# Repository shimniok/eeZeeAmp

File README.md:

eeZeeAmp is a breakout board for a standard LM386 audio amplifier circuit making it convenient to add audio
amplification to your breadboard projects.

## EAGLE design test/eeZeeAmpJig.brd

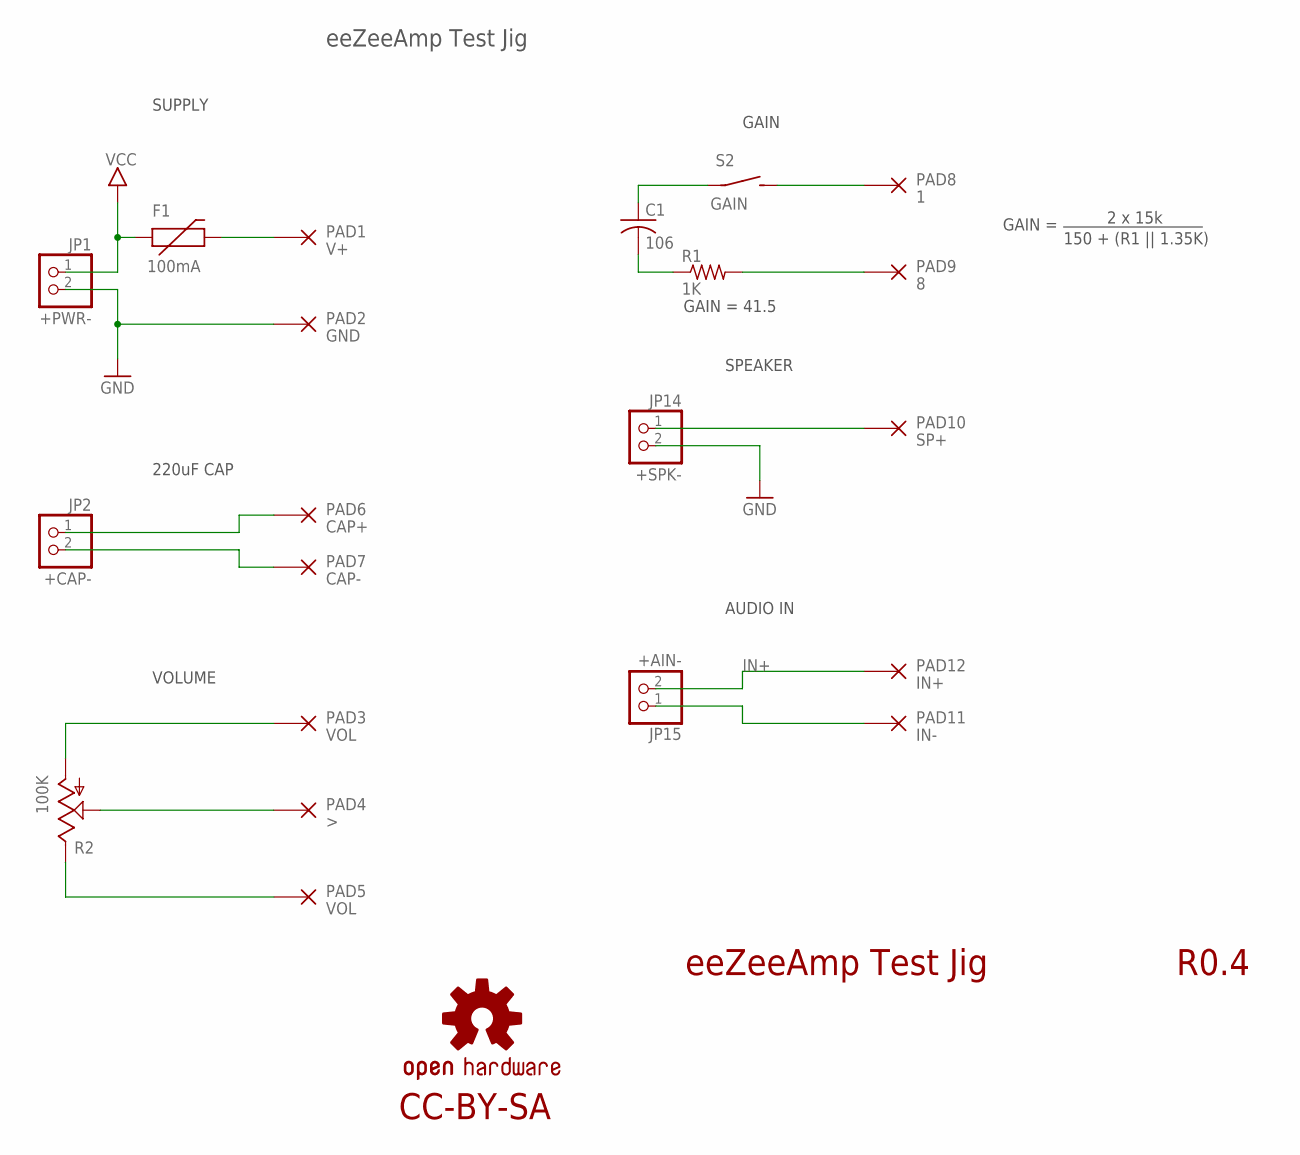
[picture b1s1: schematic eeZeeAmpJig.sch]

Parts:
C1: 106; C0805
F1: 100mA; 0603
JP1: +PWR-; 1X02-S
JP2: +CAP-; 1X02-S
JP14: +SPK-; 1X02-S
JP15: +AIN-; 1X02-S
LOGO2: OSHW-LOGOS; OSHW-LOGO-S
PAD1: V+; POGO_1.02MM
PAD2: GND; POGO_1.02MM
PAD3, PAD5: VOL; POGO_1.02MM
PAD4: >; POGO_1.02MM
PAD6: CAP+; POGO_1.02MM
PAD7: CAP-; POGO_1.02MM
PAD8: 1; POGO_1.02MM
PAD9: 8; POGO_1.02MM
PAD10: SP+; POGO_1.02MM
PAD11: IN-; POGO_1.02MM
PAD12: IN+; POGO_1.02MM
R1: 1K; R0603
R2: 100K; CA6H
S2: GAIN; 3X4X2TACT

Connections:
1: C1.1, S2.P$1
3: PAD4.P$1, R2.S
8: PAD9.P$1, R1.2
GND: JP1.2, JP14.2, PAD2.P$1
IN+: JP15.2, PAD12.P$1
IN-: JP15.1, PAD11.P$1
unnamed: PAD8.P$1, S2.P$2 (S)
unnamed: JP2.1, PAD6.P$1
unnamed: PAD5.P$1, R2.E
unnamed: F1.2, PAD1.P$1
unnamed: C1.2, R1.1
unnamed: JP2.2, PAD7.P$1
unnamed: PAD3.P$1, R2.A
SPEAKER: JP14.1, PAD10.P$1
VCC: F1.1, JP1.1

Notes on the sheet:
eeZeeAmp Test Jig
R0.4
GAIN
CC-BY-SA
VOLUME
SUPPLY
AUDIO IN
SPEAKER
GAIN =
2 x 15k
150 + (R1 || 1.35K)
GAIN = 41.5
220uF CAP

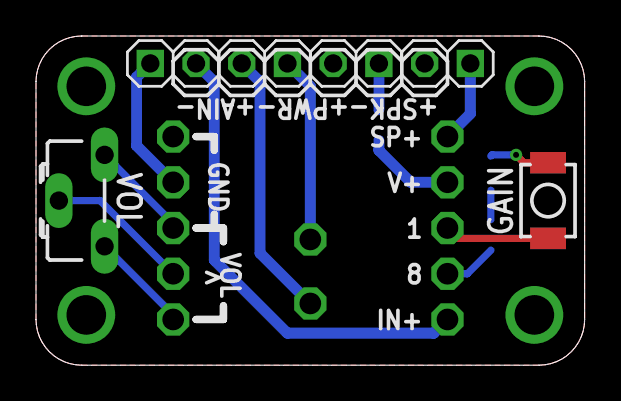
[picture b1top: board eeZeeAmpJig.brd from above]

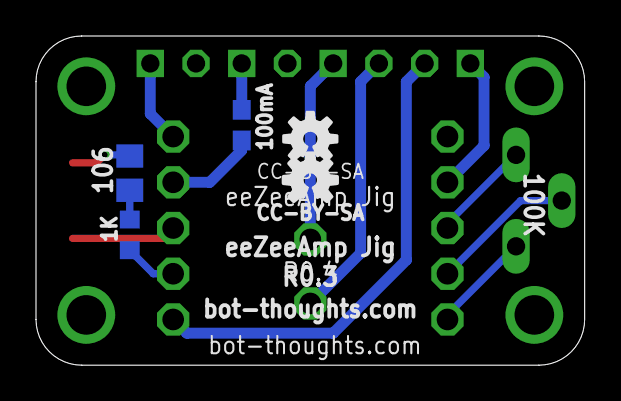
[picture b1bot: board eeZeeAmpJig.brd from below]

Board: 2 copper layers, 30.5 x 18.3 mm, 22 parts (4 on the bottom side), 15 nets.

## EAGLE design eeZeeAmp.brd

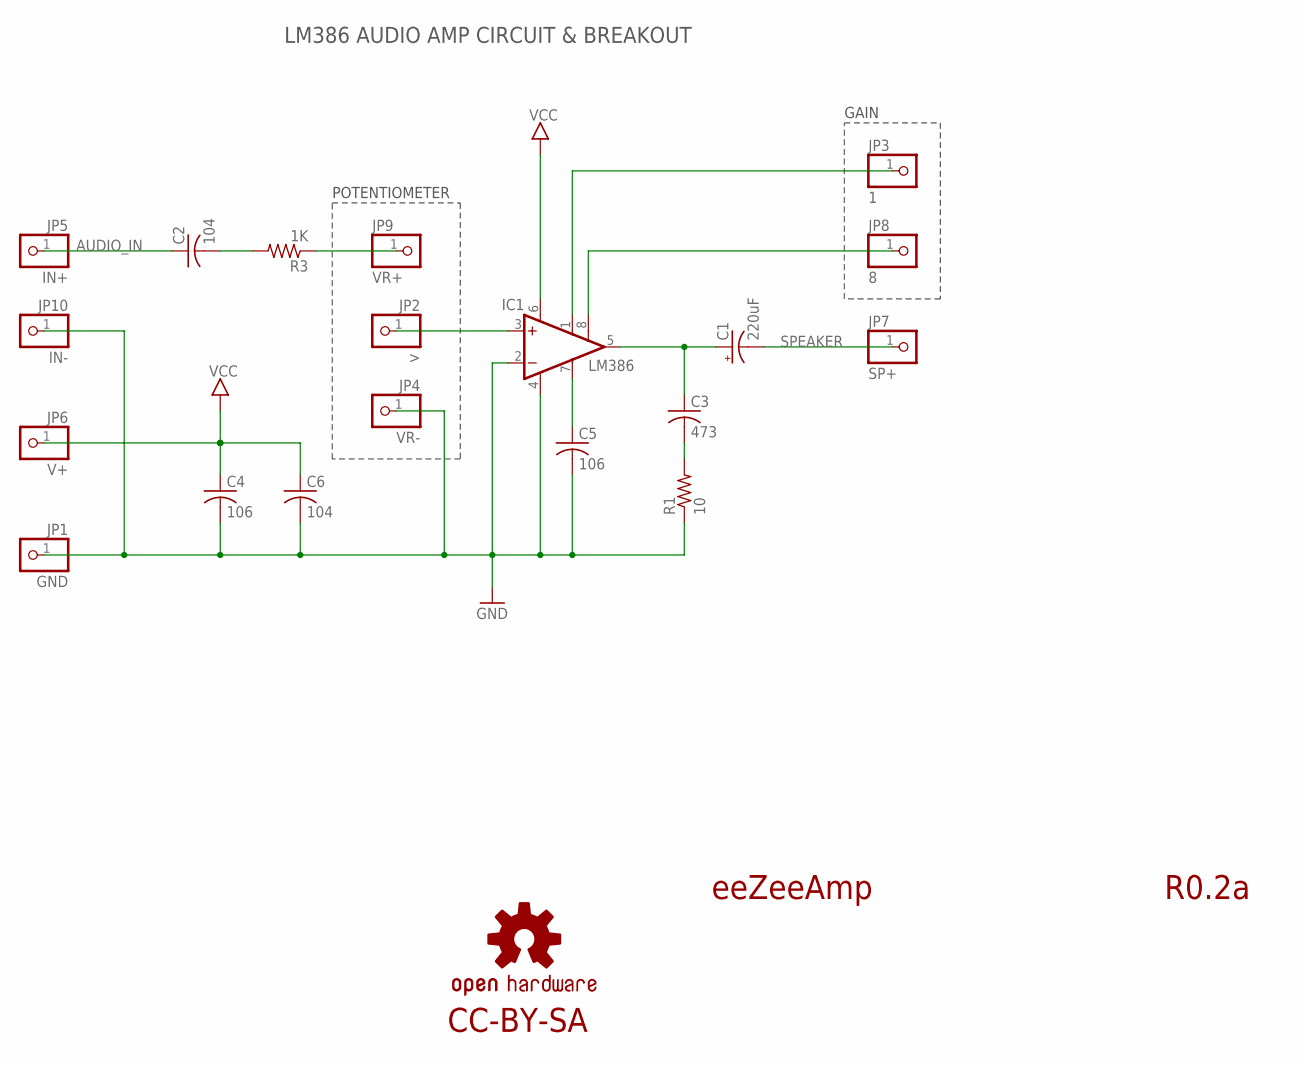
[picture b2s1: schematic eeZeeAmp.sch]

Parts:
C1: 220uF; E3,5-8
C2, C6: 104; C0603
C3: 473; C0603
C4, C5: 106; C1206
IC1: LM386; SO08
JP1: GND; 1X01-S
JP2: >; 1X01-S
JP3: 1; 1X01-S
JP4: VR-; 1X01-S
JP5: IN+; 1X01-S
JP6: V+; 1X01-S
JP7: SP+; 1X01-S
JP8: 8; 1X01-S
JP9: VR+; 1X01-S
JP10: IN-; 1X01-S
LOGO2: OSHW-LOGOS; OSHW-LOGO-S
R1: 10; R0603
R3: 1K; R0603

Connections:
1: IC1.1 (GAIN), JP3.1
3: IC1.3 (+IN), JP2.1
5: C1.+, C3.1, IC1.5 (OUT)
7: C5.1, IC1.7 (BYPASS)
8: IC1.8 (GAIN), JP8.1
AUDIO_IN: C2.1, JP5.1
GND: C4.2, C5.2, C6.2, IC1.2 (-IN), IC1.4 (GND), JP1.1, JP4.1, JP10.1, R1.1
unnamed: C2.2, R3.2
unnamed: C3.2, R1.2
unnamed: JP9.1, R3.1
SPEAKER: C1.-, JP7.1
VCC: C4.1, C6.1, IC1.6 (VS), JP6.1

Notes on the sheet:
eeZeeAmp
R0.2a
POTENTIOMETER
LM386 AUDIO AMP CIRCUIT & BREAKOUT
GAIN
CC-BY-SA

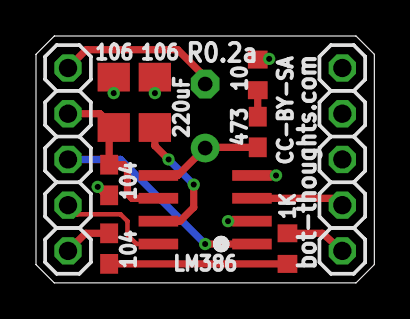
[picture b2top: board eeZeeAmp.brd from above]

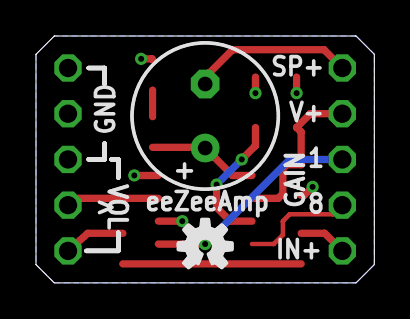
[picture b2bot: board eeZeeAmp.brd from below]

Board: 2 copper layers, 18.8 x 13.7 mm, 20 parts (2 on the bottom side), 12 nets.

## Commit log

2014-12-01 Initial revision
2014-12-01 Minor updates, added gerbers, zip
2015-01-02 Final version of silk
2015-01-02 Fixed silk pin 1 on LM386, updated version #
2015-05-01 Added 0.1uF decoupling cap for LM386 supply
2015-05-01 Replaced offboard pot with pin header for clarity
2015-05-01 Revised pinout with single ground in attempt to remove ground loop. Revised schematic to use individual pin headers
2015-05-01 Separated gain pin header into individual pins
2015-05-01 Separated variable resistor header into individual pins
2015-05-01 Aesthetic mod
2015-05-01 Added another ground pin, rearrange layout
2015-05-01 Narrowed by 0.1", complete redo of layout, text, accommodated larger 8mm output cap, fitted decoupling 0.1uF, located all gnd near to avoid loop, removed top ground pour
2015-05-01 moved label
2015-05-01 Added title, OSHW logo on both sheets, relabeled gnd, audio in gnd pin header, added gain label, added cc
2015-05-03 Created silk and gerbers
2015-05-04 Added LICENSE and README files
2015-09-28 Changed 503 cap to more common value 473
2015-09-30 Added assembly instructions
2015-10-01 Added test jig
2015-10-01 Altered gain to 40.5 with resistor, changed pot value, created silk and gerbers
2015-10-01 created zip of jig gerbers
2015-10-01 increased switch/pot clearance by embiggening board. Moved fuse to bottom layer. Changed some silk
2015-10-01 Updated gerbers
2015-10-01 updated zip
2015-10-06 Added test jig schematic
2015-10-06 Updated git ignore for ods lock files
2015-10-06 Added LM386 Calculator spreadsheet
2015-10-22 increased drill size for pogos, replaced microB with pin headers, moved power, ain, spkr pin headers, shrank board, centered pogo pin test area, reduced mounting hole drill size to #2, reduced spacer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
2015-10-22 Moved Jig files into subdirectory
2015-10-22 added pogo pins for output audio cap
2015-10-22 Fixed capacitor labels, polarity
2015-10-22 Added markdown README as user guide
2015-10-22 Added images for documentation
2015-10-22 Minor updates
2015-10-22 Removed libreoffice/pdf files
2015-10-23 changed 100k to 10k for volume
2015-10-23 moved electronics into subdirectory
2015-10-23 Added buy now link and short intro text
2015-10-23 Added table and guidance for speaker selection

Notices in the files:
parts and their libraries:
SparkFun-Aesthetics: Licensing: Creative Commons ShareAlike 4.0 International - https://creativecommons.org/licenses/by-sa/4.0
